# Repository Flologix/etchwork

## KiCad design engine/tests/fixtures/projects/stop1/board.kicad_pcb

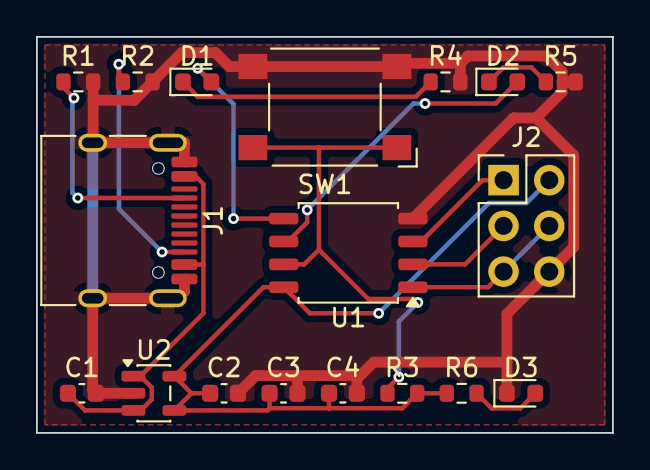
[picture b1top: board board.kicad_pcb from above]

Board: 2 copper layers, 32.0 x 22.0 mm, 18 parts (0 on the bottom side), 14 nets.

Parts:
C1, C2: 4.7uF; C_0603_1608Metric
C3, C4: 0.1uF; C_0603_1608Metric
D1: LED Green; LED_0603_1608Metric
D2: LED Red; LED_0603_1608Metric
D3: LED Yellow; LED_0603_1608Metric
J1: USB-C receptacle; USB_C_Receptacle_HRO_TYPE-C-31-M-12
J2: ISP header 2x3; PinHeader_2x03_P2.54mm_Vertical
R1, R2: 5.1k; R_0603_1608Metric
R3: 10k; R_0603_1608Metric
R4, R5, R6: 470; R_0603_1608Metric
SW1: B3FS-1000P; SW_SPST_Omron_B3FS-100xP
U1: ATtiny85-20SSU; SOIC-8_5.3x5.3mm_P1.27mm
U2: MIC5219-3.3YM5; SOT-23-5

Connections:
BTN: R3.1, SW1.1, U1.7
CC1: J1.A5, R1.1
CC2: J1.B5, R2.1
GND: C1.2, C2.2, C3.2, C4.2, D3.1, J1.A1, J1.A12, J1.B1, J1.B12, J1.SH, J2.6, R1.2, R2.2, R4.2, R5.2, SW1.2, U1.4, U2.2
ISP_MISO: J2.1, U1.3
ISP_MOSI_RST: J2.4, J2.5, U1.1
ISP_SCK: J2.3, U1.2
LED1: D1.2, U1.5
LED1_K: D1.1, R4.1
LED2: D2.2, U1.6
LED2_K: D2.1, R5.1
LED_PWR: D3.2, R6.2
USB_5V: C1.1, J1.A4, J1.A9, J1.B4, J1.B9, U2.1, U2.3
VCC_3V3: C2.1, C3.1, C4.1, J2.2, R3.2, R6.1, U1.8, U2.4, U2.5
